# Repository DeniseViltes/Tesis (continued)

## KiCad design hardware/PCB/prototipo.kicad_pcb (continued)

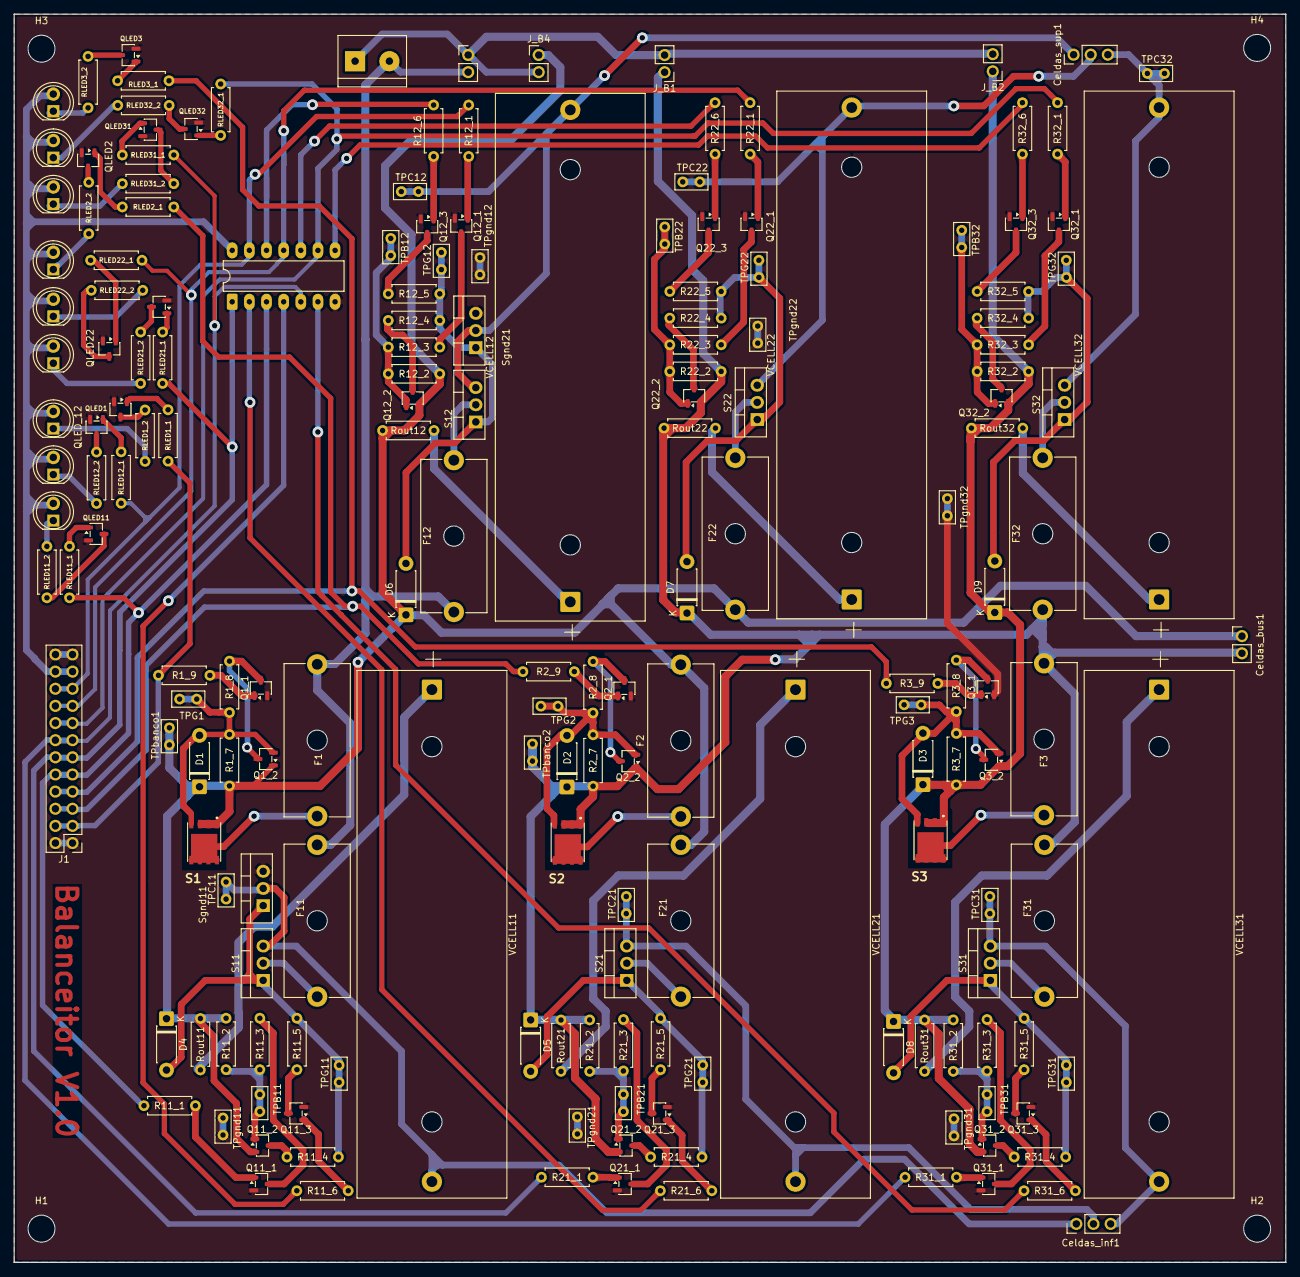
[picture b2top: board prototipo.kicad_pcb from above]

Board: 2 copper layers, 188.4 x 185.0 mm, 189 parts (0 on the bottom side), 121 nets.

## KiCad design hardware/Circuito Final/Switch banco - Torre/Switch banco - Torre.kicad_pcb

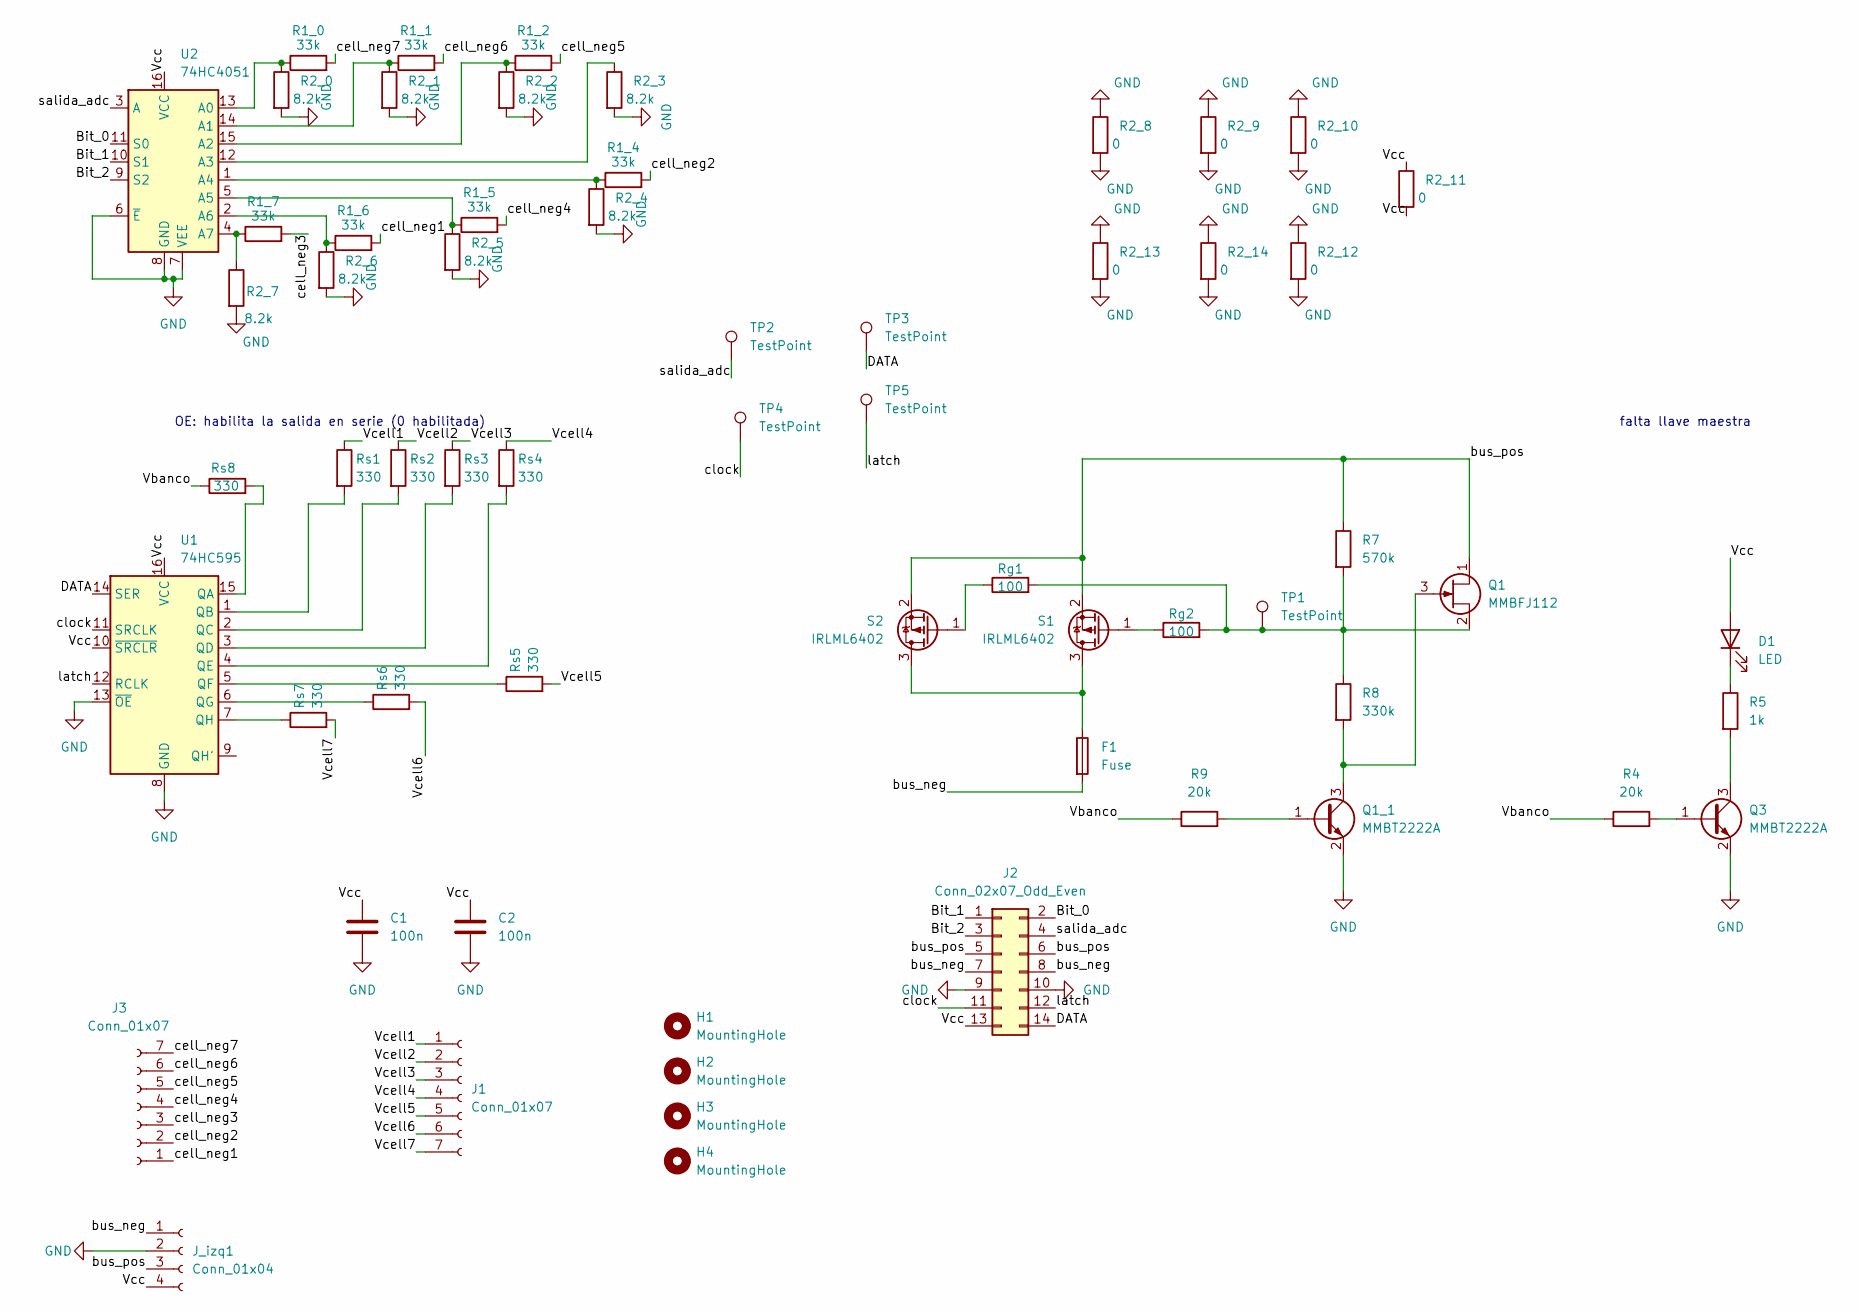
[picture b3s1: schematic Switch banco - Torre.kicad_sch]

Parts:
C1, C2: 100n; C_1206_3216Metric_Pad1.33x1.80mm_HandSolder
D1: LED; LED_D5.0mm
F1: Fuse; Fuse_1206_3216Metric_Pad1.42x1.75mm_HandSolder
H1, H2, H3, H4: MountingHole; MountingHole_3.5mm
J1, J3: Conn_01x07; PinSocket_1x07_P2.54mm_Vertical
J2: Conn_02x07_Odd_Even; IDC-Header_2x07_P2.54mm_Horizontal
J_izq1: Conn_01x04; PinSocket_1x04_P2.54mm_Vertical
Q1: MMBFJ112; SOT-23_Handsoldering
Q1_1, Q3: MMBT2222A; SOT-23_Handsoldering
R1_0, R1_1, R1_2, R1_4, R1_5, R1_6, R1_7: 33k; R_1206_3216Metric_Pad1.30x1.75mm_HandSolder
R2_0, R2_1, R2_2, R2_3, R2_4, R2_5, R2_6, R2_7: 8.2k; R_1206_3216Metric_Pad1.30x1.75mm_HandSolder
R2_8, R2_9, R2_10, R2_11, R2_12, R2_13, R2_14: 0; R_1206_3216Metric_Pad1.30x1.75mm_HandSolder
R4, R9: 20k; R_1206_3216Metric_Pad1.30x1.75mm_HandSolder
R5: 1k; R_1206_3216Metric_Pad1.30x1.75mm_HandSolder
R7: 570k; R_1206_3216Metric_Pad1.30x1.75mm_HandSolder
R8: 330k; R_1206_3216Metric_Pad1.30x1.75mm_HandSolder
Rg1, Rg2: 100; R_1206_3216Metric_Pad1.30x1.75mm_HandSolder
Rs1, Rs2, Rs3, Rs4, Rs5, Rs6, Rs7, Rs8: 330; R_1206_3216Metric_Pad1.30x1.75mm_HandSolder
S1, S2: IRLML6402; SOT-23_Handsoldering
TP1, TP2, TP3, TP4, TP5: TestPoint; TestPoint_Loop_D2.54mm_Drill1.5mm_Beaded
U1: 74HC595; SOIC-16_3.9x9.9mm_P1.27mm
U2: 74HC4051; SOIC-16_3.9x9.9mm_P1.27mm

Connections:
/Bit_0: J2.2, U2.11 (S0)
/Bit_1: J2.1, U2.10 (S1)
/Bit_2: J2.3, U2.9 (S2)
/DATA: J2.14, TP3.1 (1_1), U1.14 (SER)
/Vbanco: R4.1, R9.1, Rs8.1
/Vcc: C1.1, C2.1, D1.2 (A), J2.13, J_izq1.4, R2_11.1, R2_11.2, U1.10 (~SRCLR), U1.16 (VCC), U2.16 (VCC)
/Vcell1: J1.1, Rs1.1
/Vcell2: J1.2, Rs2.1
/Vcell3: J1.3, Rs3.1
/Vcell4: J1.4, Rs4.1
/Vcell5: J1.5, Rs5.2
/Vcell6: J1.6, Rs6.2
/Vcell7: J1.7, Rs7.2
/bus_neg: F1.2, J2.7, J2.8, J_izq1.1
/bus_pos: J2.5, J2.6, J_izq1.3, Q1.1 (D), R7.1, S1.2 (S), S2.2 (S)
/cell_neg1: J3.1, R1_6.2
/cell_neg2: J3.2, R1_4.2
/cell_neg3: J3.3, R1_7.2
/cell_neg4: J3.4, R1_5.2
/cell_neg5: J3.5, R1_2.2
/cell_neg6: J3.6, R1_1.2
/cell_neg7: J3.7, R1_0.2
/clock: J2.11, TP4.1 (1_1), U1.11 (SRCLK)
/latch: J2.12, TP5.1 (1_1), U1.12 (RCLK)
/salida_adc: J2.4, TP2.1 (1_1), U2.3 (A)
GND: C1.2, C2.2, J2.9, J2.10, J_izq1.2, Q1_1.2 (E), Q3.2 (E), R2_0.2, R2_1.2, R2_2.2, R2_3.2, R2_4.2, R2_5.2, R2_6.2, R2_7.2, R2_8.1, R2_8.2, R2_9.1, R2_9.2, R2_10.1, R2_10.2, R2_12.1, R2_12.2, R2_13.1, R2_13.2, R2_14.1, R2_14.2, U1.8 (GND), U1.13 (~OE), U2.6 (~E), U2.7 (VEE), U2.8 (GND)
unnamed: D1.1 (K), R5.1
unnamed: Q1.3 (G), Q1_1.3 (C), R8.2
unnamed: Q1.2 (S), R7.2, R8.1, Rg1.2, Rg2.2, TP1.1 (1_1)
unnamed: Q1_1.1 (B), R9.2
unnamed: Q3.1 (B), R4.2
unnamed: Q3.3 (C), R5.2
unnamed: F1.1, S1.3 (D), S2.3 (D)
unnamed: Rg2.1, S1.1 (G)
unnamed: Rg1.1, S2.1 (G)
unnamed: Rs8.2, U1.15 (QA)
unnamed: Rs1.2, U1.1 (QB)
unnamed: Rs2.2, U1.2 (QC)
unnamed: Rs3.2, U1.3 (QD)
unnamed: Rs4.2, U1.4 (QE)
unnamed: Rs5.1, U1.5 (QF)
unnamed: Rs6.1, U1.6 (QG)
unnamed: Rs7.1, U1.7 (QH)
unnamed: R1_0.1, R2_0.1, U2.13 (A0)
unnamed: R1_1.1, R2_1.1, U2.14 (A1)
unnamed: R1_2.1, R2_2.1, U2.15 (A2)
unnamed: R2_3.1, U2.12 (A3)
unnamed: R1_4.1, R2_4.1, U2.1 (A4)
unnamed: R1_5.1, R2_5.1, U2.5 (A5)
unnamed: R1_6.1, R2_6.1, U2.2 (A6)
unnamed: R1_7.1, R2_7.1, U2.4 (A7)

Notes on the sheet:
falta llave maestra
OE: habilita la salida en serie (0 habilitada)

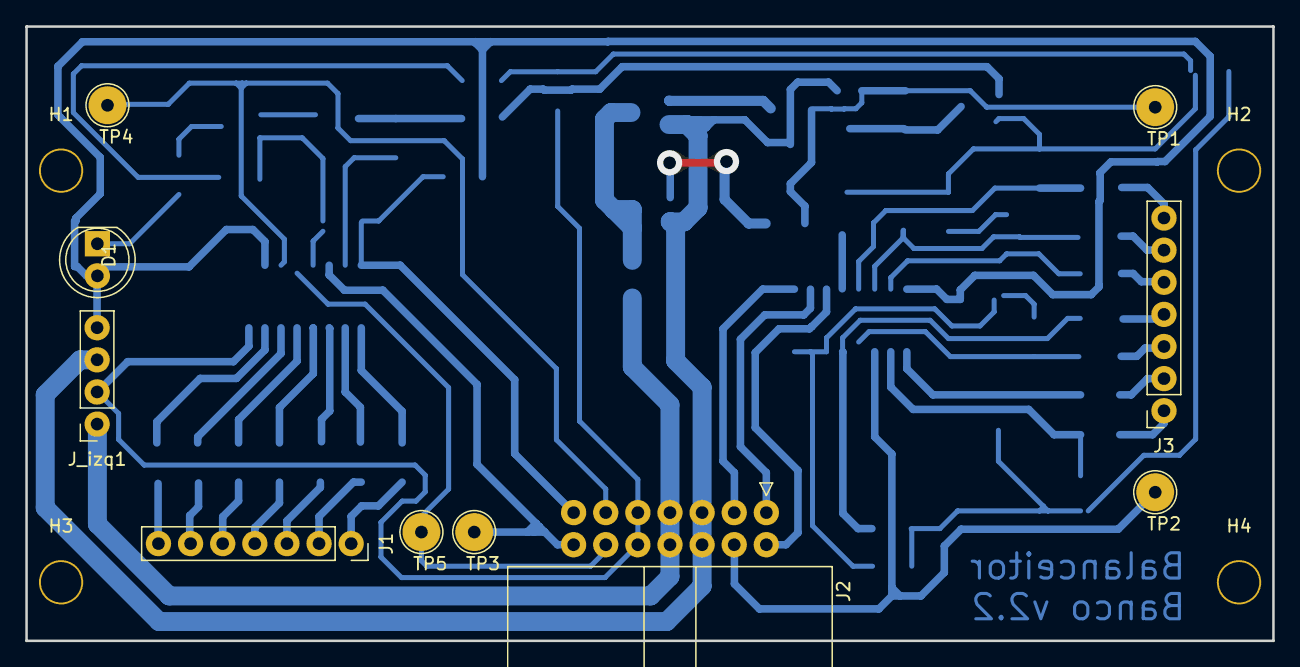
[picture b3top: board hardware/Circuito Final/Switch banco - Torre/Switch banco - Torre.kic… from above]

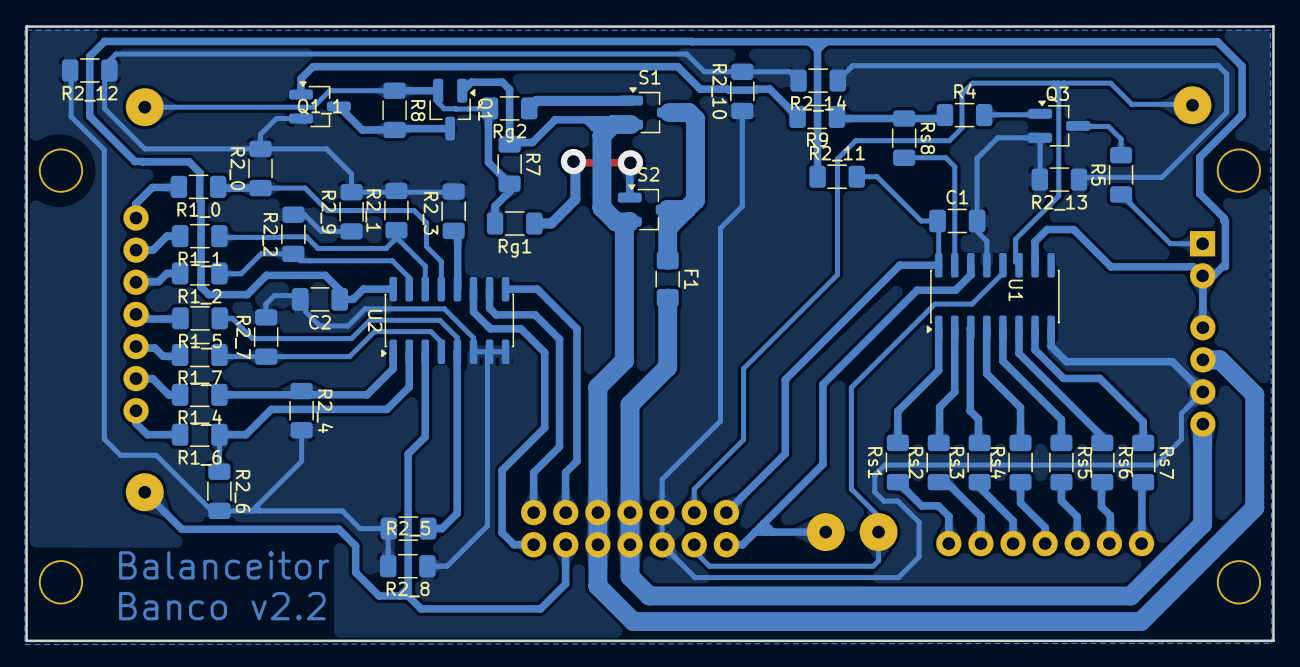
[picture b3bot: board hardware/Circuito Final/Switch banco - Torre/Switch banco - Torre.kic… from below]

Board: 2 copper layers, 98.6 x 48.6 mm, 61 parts (47 on the bottom side), 51 nets.

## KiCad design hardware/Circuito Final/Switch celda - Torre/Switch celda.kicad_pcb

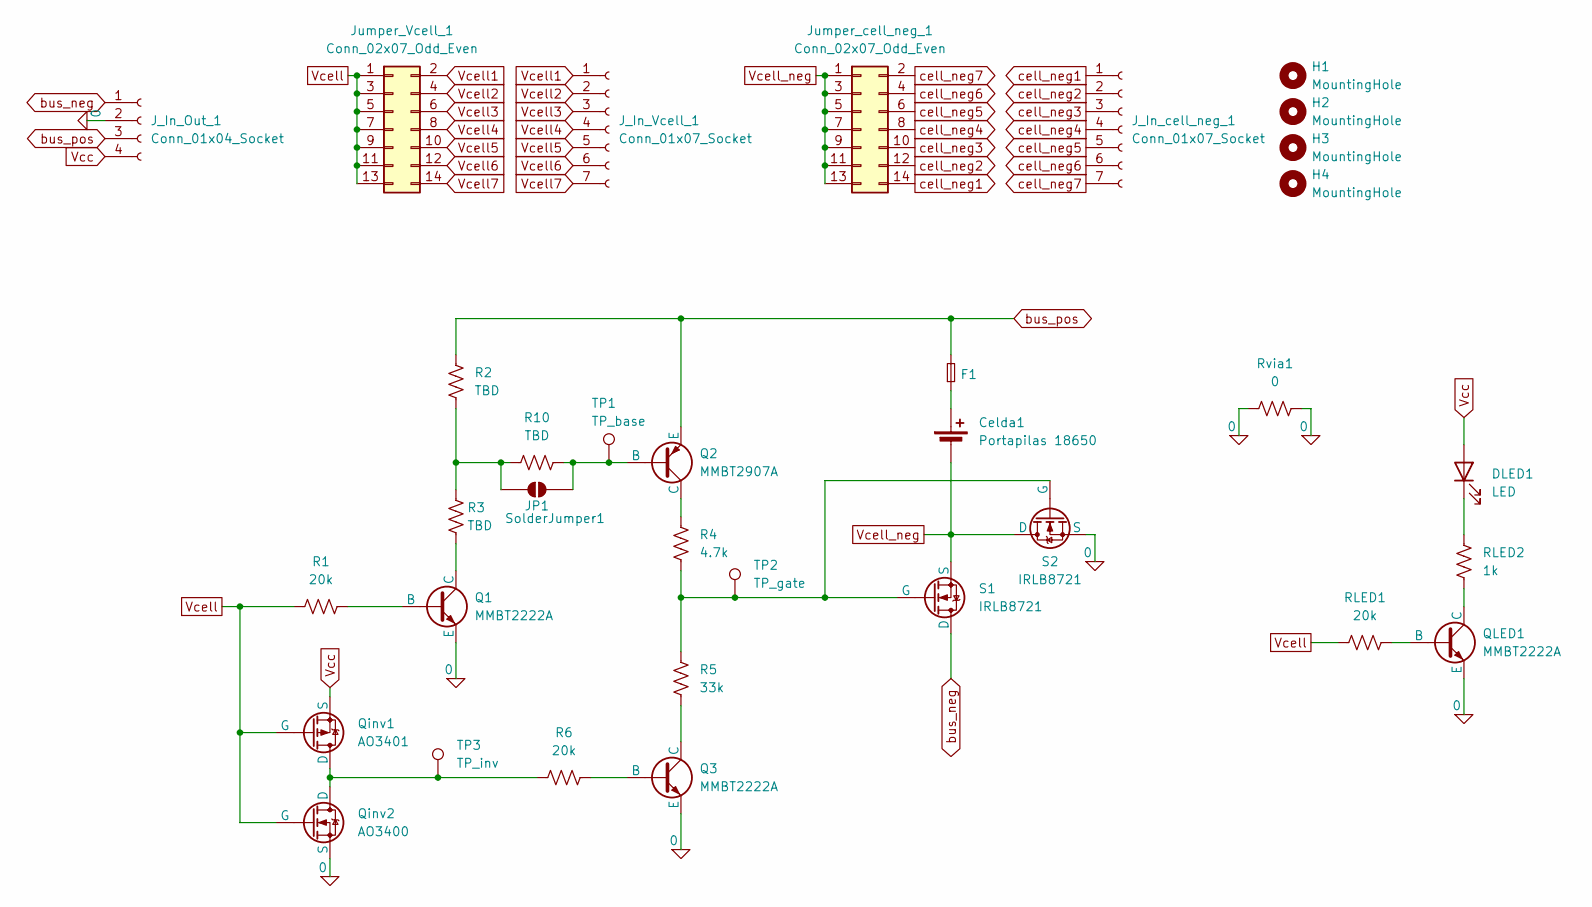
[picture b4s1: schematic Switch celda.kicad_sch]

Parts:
Celda1: Portapilas 18650; BatteryHolder_MPD_BK-18650-PC2
DLED1: LED; LED_D5.0mm
F1: Fuse_1206_3216Metric_Pad1.42x1.75mm_HandSolder
H1, H2, H3, H4: MountingHole; MountingHole_3.5mm
JP1: SolderJumper1; SolderJumper-2_P1.3mm_Open_TrianglePad1.0x1.5mm
J_In_Out_1: Conn_01x04_Socket; PinSocket_1x04_P2.54mm_Vertical
J_In_Vcell_1: Conn_01x07_Socket; PinSocket_1x07_P2.54mm_Vertical
J_In_cell_neg_1: Conn_01x07_Socket; PinSocket_1x07_P2.54mm_Vertical
Jumper_Vcell_1: Conn_02x07_Odd_Even; PinHeader_2x07_P2.54mm_Vertical
Jumper_cell_neg_1: Conn_02x07_Odd_Even; PinHeader_2x07_P2.54mm_Vertical
Q1, Q3: MMBT2222A; SOT-23_Handsoldering
Q2: MMBT2907A; SOT-23_Handsoldering
QLED1: MMBT2222A; SOT-23_Handsoldering
Qinv1: AO3401; SOT-23_Handsoldering
Qinv2: AO3400; SOT-23_Handsoldering
R1, R6: 20k; R_1206_3216Metric_Pad1.30x1.75mm_HandSolder
R2, R3, R10: TBD; R_1206_3216Metric_Pad1.30x1.75mm_HandSolder
R4: 4.7k; R_1206_3216Metric_Pad1.30x1.75mm_HandSolder
R5: 33k; R_1206_3216Metric_Pad1.30x1.75mm_HandSolder
RLED1: 20k; R_1206_3216Metric_Pad1.30x1.75mm_HandSolder
RLED2: 1k; R_1206_3216Metric_Pad1.30x1.75mm_HandSolder
Rvia1: 0; R_1206_3216Metric_Pad1.30x1.75mm_HandSolder
S1, S2: IRLB8721; TO-220-3_Vertical
TP1: TP_base; TestPoint_Loop_D2.54mm_Drill1.5mm_Beaded
TP2: TP_gate; TestPoint_Loop_D2.54mm_Drill1.5mm_Beaded
TP3: TP_inv; TestPoint_Loop_D2.54mm_Drill1.5mm_Beaded

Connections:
0: J_In_Out_1.2, Q1.3 (E), Q3.3 (E), QLED1.3 (E), Qinv2.3 (S), Rvia1.1, Rvia1.2, S2.3 (S)
unnamed: Celda1.1 (+), F1.1
unnamed: DLED1.1 (K), RLED2.2
unnamed: JP1.1 (A), R2.1, R3.2, R10.1
unnamed: JP1.2 (B), Q2.2 (B), R10.2, TP1.1 (1_1)
unnamed: Q1.2 (B), R1.2
unnamed: Q1.1 (C), R3.1
unnamed: Q2.1 (C), R4.2
unnamed: Q3.2 (B), R6.2
unnamed: Q3.1 (C), R5.1
unnamed: QLED1.2 (B), RLED1.2
unnamed: QLED1.1 (C), RLED2.1
unnamed: Qinv1.1 (D), Qinv2.1 (D), R6.1, TP3.1 (1_1)
unnamed: R4.1, R5.2, S1.2 (G), S2.2 (G), TP2.1 (1_1)
Vcc: DLED1.2 (A), J_In_Out_1.4, Qinv1.3 (S)
Vcell: Jumper_Vcell_1.1, Jumper_Vcell_1.3, Jumper_Vcell_1.5, Jumper_Vcell_1.7, Jumper_Vcell_1.9, Jumper_Vcell_1.11, Jumper_Vcell_1.13, Qinv1.2 (G), Qinv2.2 (G), R1.1, RLED1.1
Vcell1: J_In_Vcell_1.1, Jumper_Vcell_1.2
Vcell2: J_In_Vcell_1.2, Jumper_Vcell_1.4
Vcell3: J_In_Vcell_1.3, Jumper_Vcell_1.6
Vcell4: J_In_Vcell_1.4, Jumper_Vcell_1.8
Vcell5: J_In_Vcell_1.5, Jumper_Vcell_1.10
Vcell6: J_In_Vcell_1.6, Jumper_Vcell_1.12
Vcell7: J_In_Vcell_1.7, Jumper_Vcell_1.14
Vcell_neg: Celda1.2 (-), Jumper_cell_neg_1.1, Jumper_cell_neg_1.3, Jumper_cell_neg_1.5, Jumper_cell_neg_1.7, Jumper_cell_neg_1.9, Jumper_cell_neg_1.11, Jumper_cell_neg_1.13, S1.3 (S), S2.1 (D)
bus_neg: J_In_Out_1.1, S1.1 (D)
bus_pos: F1.2, J_In_Out_1.3, Q2.3 (E), R2.2
cell_neg1: J_In_cell_neg_1.1, Jumper_cell_neg_1.14
cell_neg2: J_In_cell_neg_1.2, Jumper_cell_neg_1.12
cell_neg3: J_In_cell_neg_1.3, Jumper_cell_neg_1.10
cell_neg4: J_In_cell_neg_1.4, Jumper_cell_neg_1.8
cell_neg5: J_In_cell_neg_1.5, Jumper_cell_neg_1.6
cell_neg6: J_In_cell_neg_1.6, Jumper_cell_neg_1.4
cell_neg7: J_In_cell_neg_1.7, Jumper_cell_neg_1.2

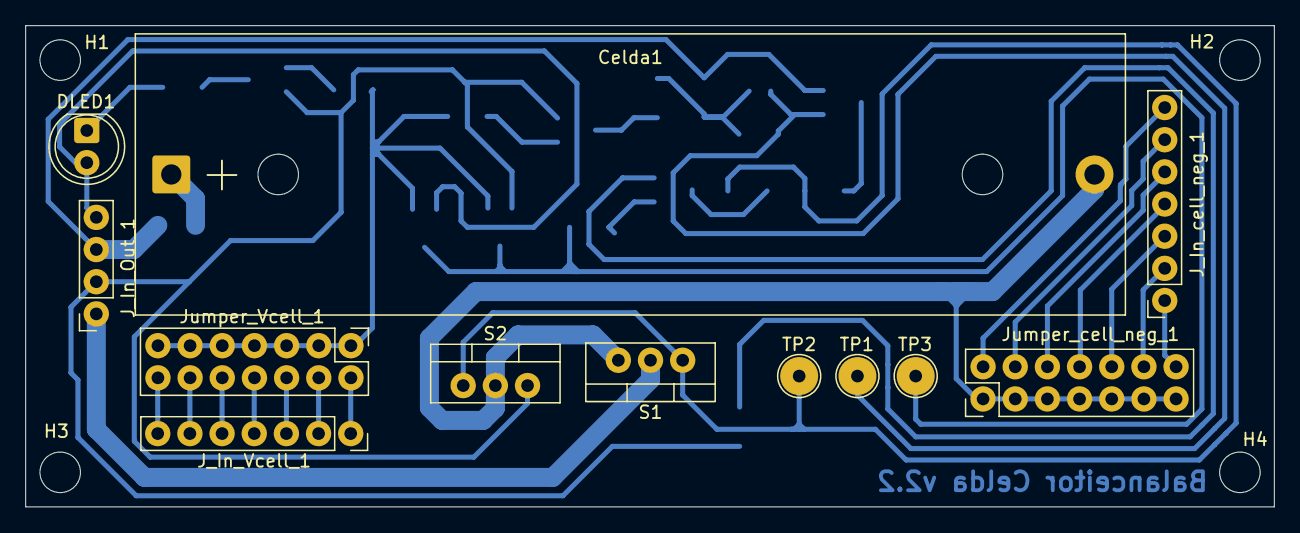
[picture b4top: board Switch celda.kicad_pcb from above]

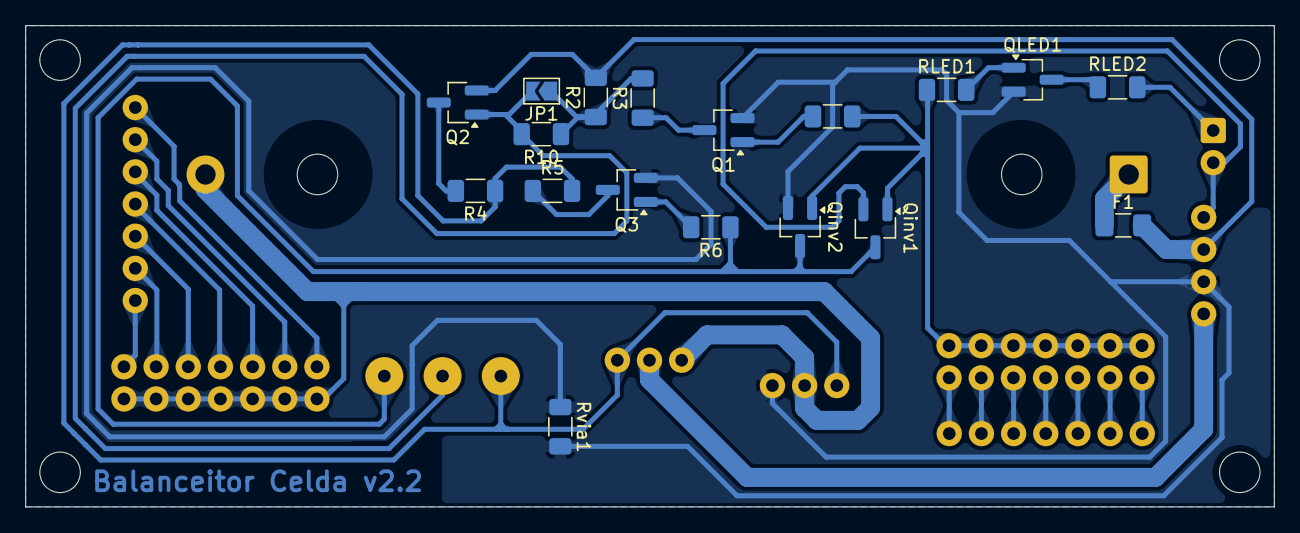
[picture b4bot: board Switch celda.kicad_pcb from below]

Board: 2 copper layers, 98.6 x 38.0 mm, 34 parts (18 on the bottom side), 33 nets.

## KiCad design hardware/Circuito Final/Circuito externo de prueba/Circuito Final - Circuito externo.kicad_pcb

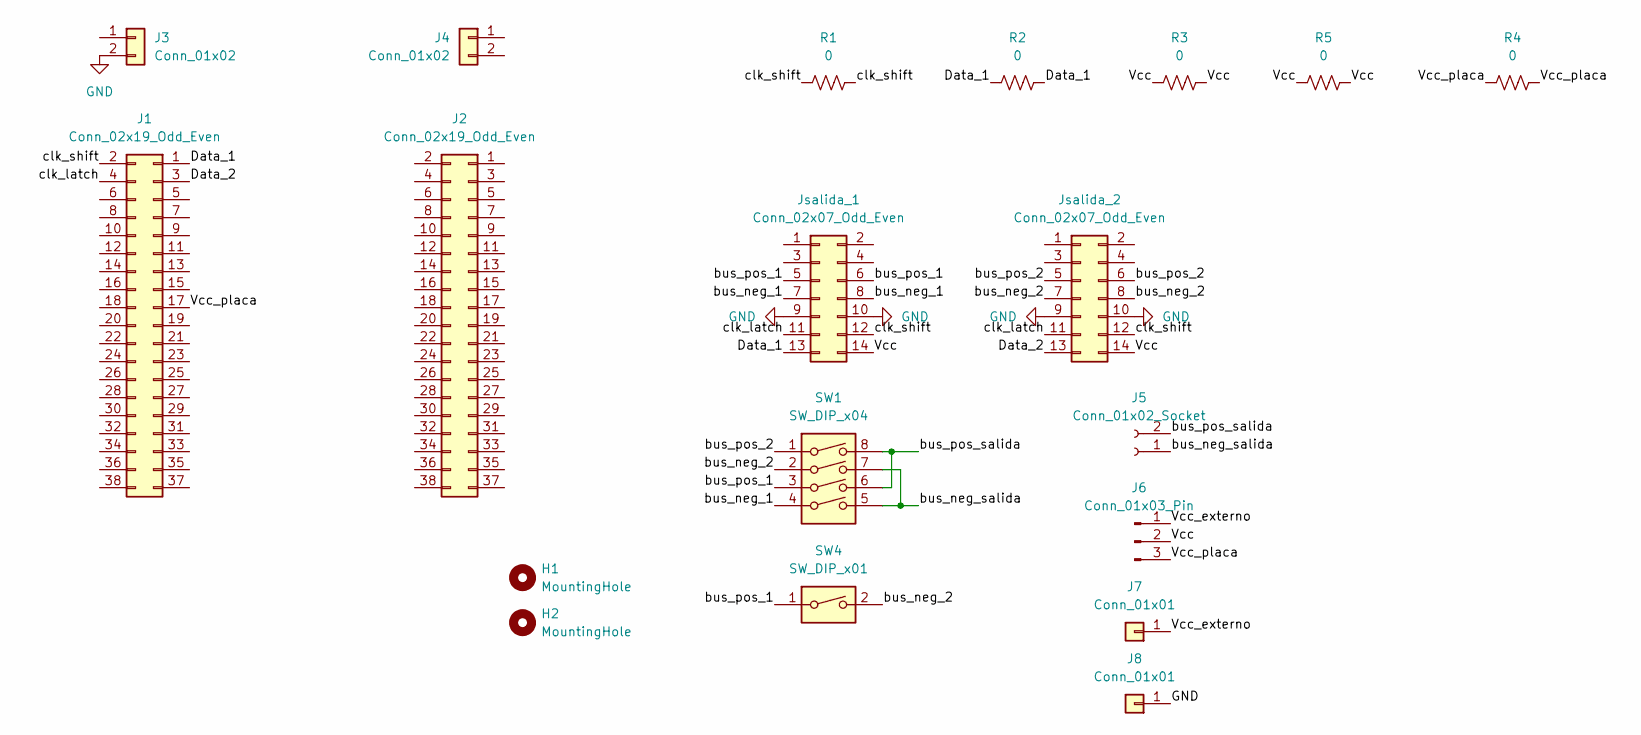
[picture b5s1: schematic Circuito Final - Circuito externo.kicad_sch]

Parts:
H1, H2: MountingHole; MountingHole_3mm
J1, J2: Conn_02x19_Odd_Even; PinSocket_2x19_P2.54mm_Vertical
J3, J4: Conn_01x02; PinSocket_1x02_P2.54mm_Vertical
J5: Conn_01x02_Socket; TerminalBlock_MaiXu_MX126-5.0-02P_1x02_P5.00mm
J6: Conn_01x03_Pin; PinHeader_1x03_P2.54mm_Vertical
J7, J8: Conn_01x01; PinHeader_1x01_P2.54mm_Vertical
Jsalida_1, Jsalida_2: Conn_02x07_Odd_Even; PinHeader_2x07_P2.54mm_Vertical
R1, R2, R3, R4, R5: 0; R_1206_3216Metric_Pad1.30x1.75mm_HandSolder
SW1: SW_DIP_x04; SW_DIP_SPSTx04_Slide_9.78x12.34mm_W7.62mm_P2.54mm
SW4: SW_DIP_x01; SW_DIP_SPSTx01_Slide_9.78x4.72mm_W7.62mm_P2.54mm

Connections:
/Data_1: J1.1, Jsalida_1.13, R2.1, R2.2
/Data_2: J1.3, Jsalida_2.13
/Vcc: J6.2, Jsalida_1.14, Jsalida_2.14, R3.1, R3.2, R5.1, R5.2
/Vcc_externo: J6.1, J7.1 (Pin_1_1)
/Vcc_placa: J1.17, J6.3, R4.1, R4.2
/bus_neg_1: Jsalida_1.7, Jsalida_1.8, SW1.4
/bus_neg_2: Jsalida_2.7, Jsalida_2.8, SW1.2, SW4.2
/bus_neg_salida: J5.1, SW1.5, SW1.7
/bus_pos_1: Jsalida_1.5, Jsalida_1.6, SW1.3, SW4.1
/bus_pos_2: Jsalida_2.5, Jsalida_2.6, SW1.1
/bus_pos_salida: J5.2, SW1.6, SW1.8
/clk_latch: J1.4, Jsalida_1.11, Jsalida_2.11
/clk_shift: J1.2, Jsalida_1.12, Jsalida_2.12, R1.1, R1.2
GND: J3.2 (Pin_2_2), J8.1 (Pin_1_1), Jsalida_1.9, Jsalida_1.10, Jsalida_2.9, Jsalida_2.10

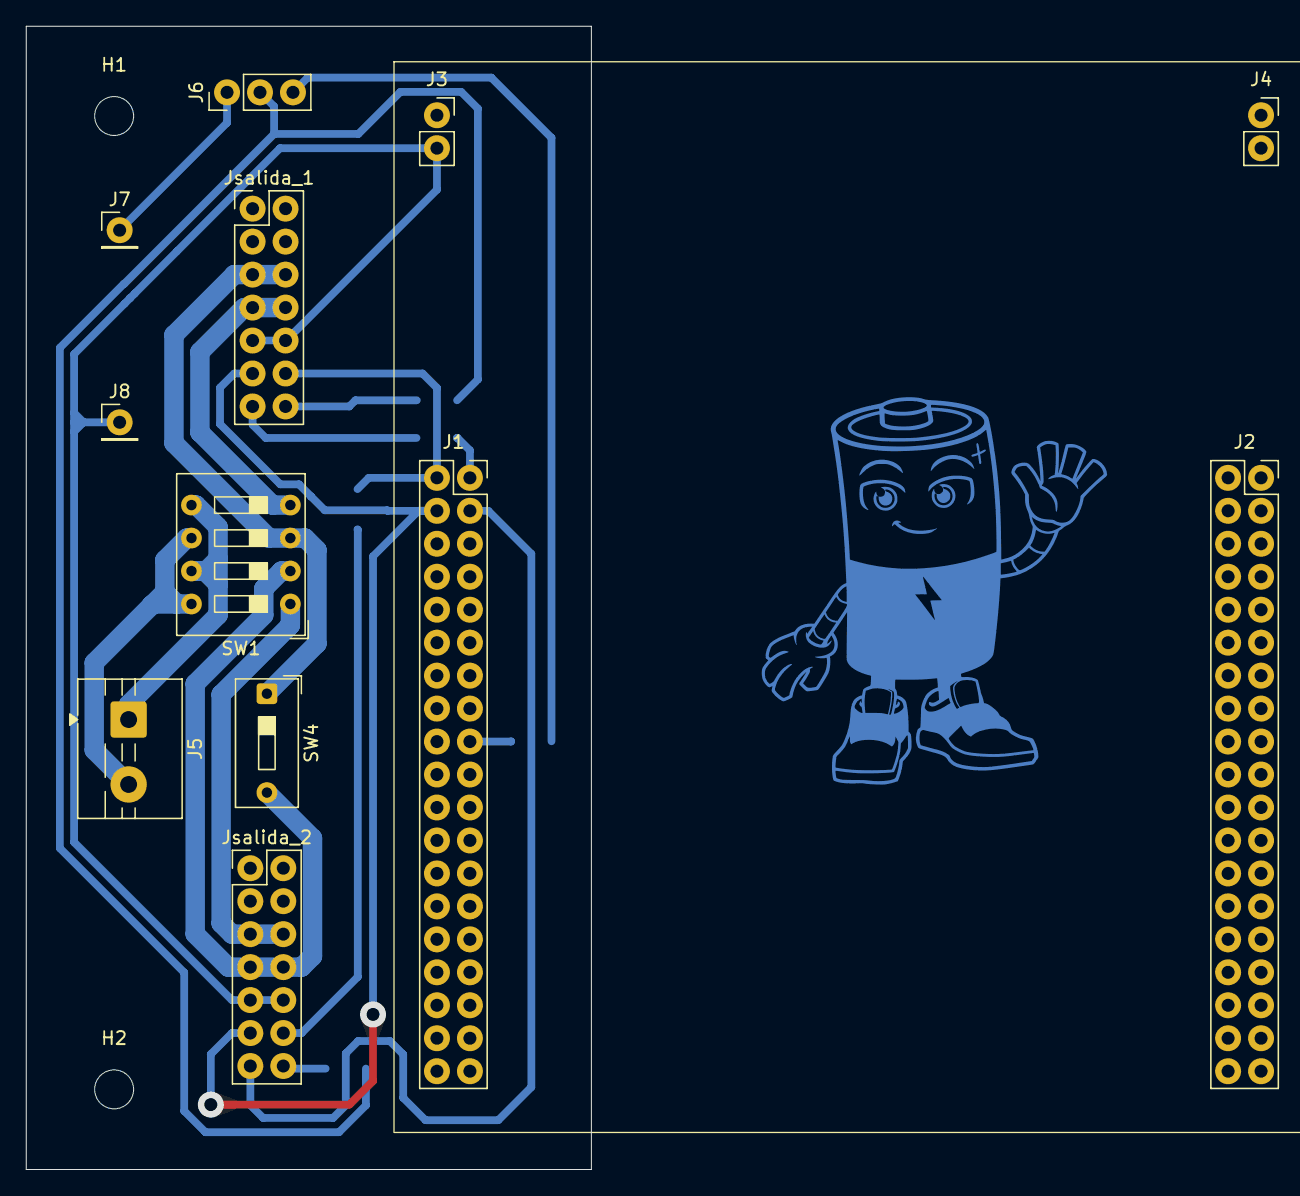
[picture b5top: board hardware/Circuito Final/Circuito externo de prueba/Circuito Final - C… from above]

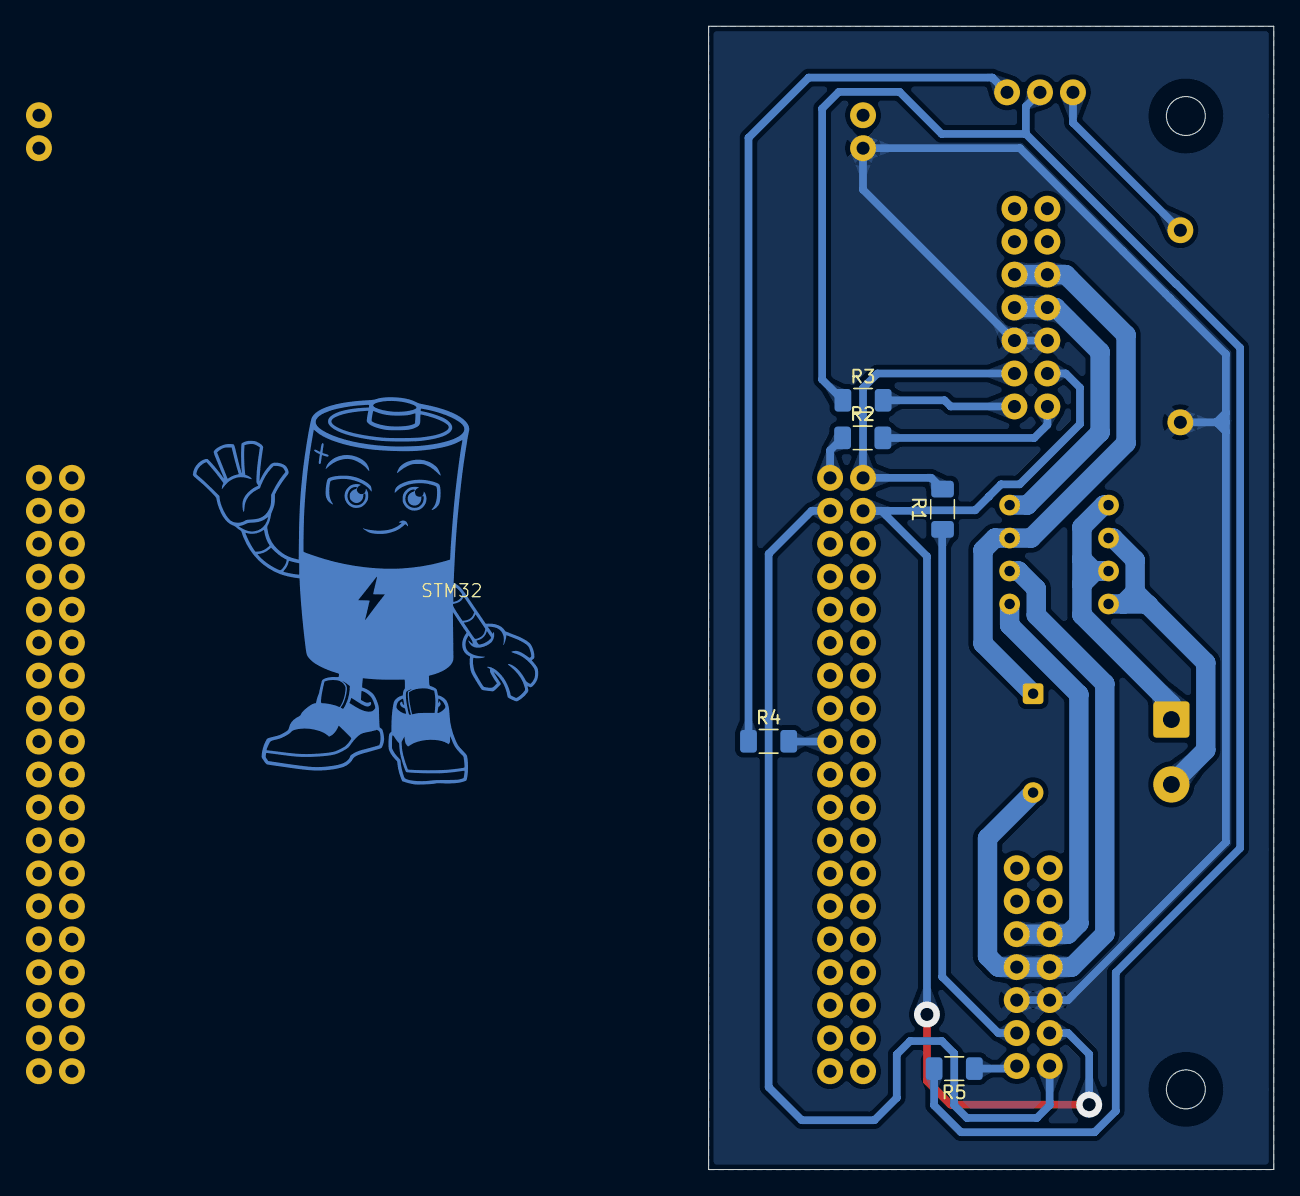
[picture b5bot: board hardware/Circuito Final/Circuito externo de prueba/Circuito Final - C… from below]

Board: 2 copper layers, 43.5 x 88.1 mm, 20 parts (5 on the bottom side), 14 nets.

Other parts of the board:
STM32: STM32

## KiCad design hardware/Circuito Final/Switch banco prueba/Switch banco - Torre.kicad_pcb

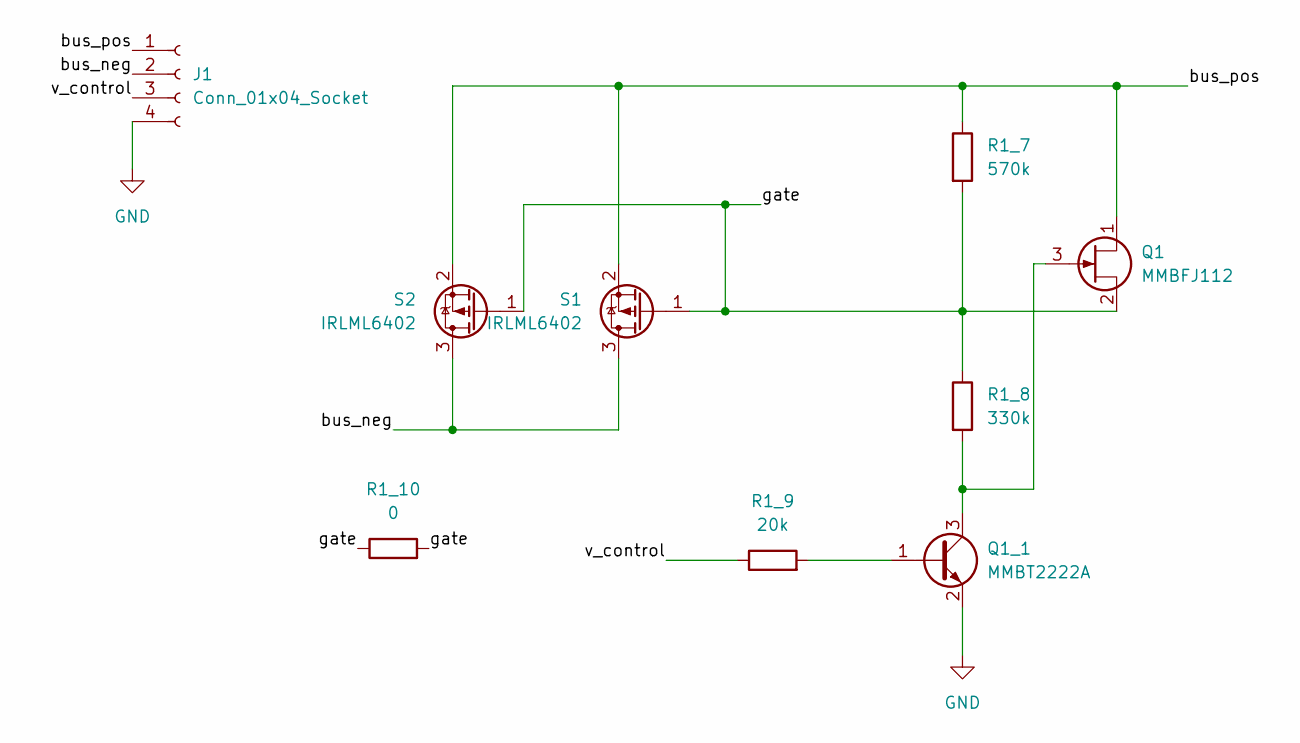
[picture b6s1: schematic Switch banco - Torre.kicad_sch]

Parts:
J1: Conn_01x04_Socket; PinSocket_1x04_P2.54mm_Vertical
Q1: MMBFJ112; SOT-23
Q1_1: MMBT2222A; SOT-23
R1_7: 570k; R_1206_3216Metric_Pad1.30x1.75mm_HandSolder
R1_8: 330k; R_1206_3216Metric_Pad1.30x1.75mm_HandSolder
R1_9: 20k; R_1206_3216Metric_Pad1.30x1.75mm_HandSolder
R1_10: 0; R_1206_3216Metric_Pad1.30x1.75mm_HandSolder
S1, S2: IRLML6402; SOT-23

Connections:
/bus_neg: J1.2, S1.3 (D), S2.3 (D)
/bus_pos: J1.1, Q1.1 (D), R1_7.1, S1.2 (S), S2.2 (S)
/gate: Q1.2 (S), R1_7.2, R1_8.1, R1_10.1, R1_10.2, S1.1 (G), S2.1 (G)
/v_control: J1.3, R1_9.1
GND: J1.4, Q1_1.2 (E)
unnamed: Q1.3 (G), Q1_1.3 (C), R1_8.2
unnamed: Q1_1.1 (B), R1_9.2

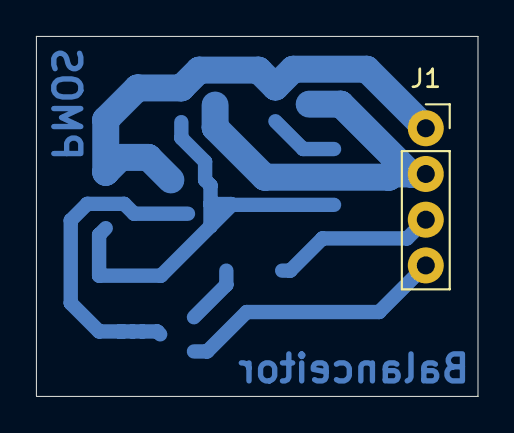
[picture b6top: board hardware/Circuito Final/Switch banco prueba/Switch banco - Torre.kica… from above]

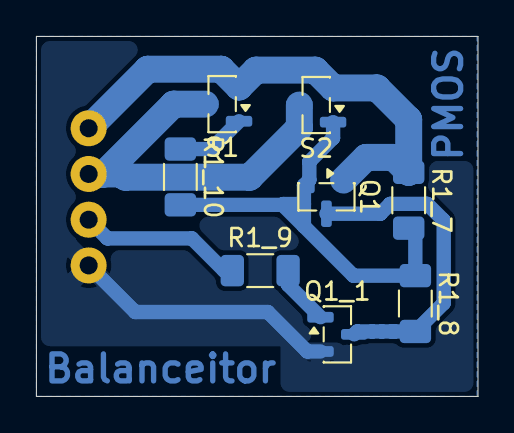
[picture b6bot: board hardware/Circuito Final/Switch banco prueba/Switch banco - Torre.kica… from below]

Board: 2 copper layers, 24.5 x 20.0 mm, 9 parts (8 on the bottom side), 7 nets.

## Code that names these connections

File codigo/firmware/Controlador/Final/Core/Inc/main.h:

/* USER CODE BEGIN Header */
/**
  ******************************************************************************
  * @file           : main.h
  * @brief          : Header for main.c file.
  *                   This file contains the common defines of the application.
  ******************************************************************************
  * @attention
  *
  * Copyright (c) 2026 STMicroelectronics.
  * All rights reserved.
  *
  * This software is licensed under terms that can be found in the LICENSE file
  * in the root directory of this software component.
  * If no LICENSE file comes with this software, it is provided AS-IS.
  *
  ******************************************************************************
  */
/* USER CODE END Header */

/* Define to prevent recursive inclusion -------------------------------------*/
#ifndef __MAIN_H
#define __MAIN_H

#ifdef __cplusplus
extern "C" {
#endif

/* Includes ------------------------------------------------------------------*/
#include "stm32f1xx_hal.h"

/* Private includes ----------------------------------------------------------*/
/* USER CODE BEGIN Includes */

/* USER CODE END Includes */

/* Exported types ------------------------------------------------------------*/
/* USER CODE BEGIN ET */

/* USER CODE END ET */

/* Exported constants --------------------------------------------------------*/
/* USER CODE BEGIN EC */

/* USER CODE END EC */

/* Exported macro ------------------------------------------------------------*/
/* USER CODE BEGIN EM */

/* USER CODE END EM */

/* Exported functions prototypes ---------------------------------------------*/
void Error_Handler(void);

/* USER CODE BEGIN EFP */

/* USER CODE END EFP */

/* Private defines -----------------------------------------------------------*/
#define DATA2_Pin GPIO_PIN_13
#define DATA2_GPIO_Port GPIOC
#define medicion_corriente_de_carga_Pin GPIO_PIN_0
#define medicion_corriente_de_carga_GPIO_Port GPIOC
#define salida_adc_2_Pin GPIO_PIN_2
#define salida_adc_2_GPIO_Port GPIOC
#define banco2_med_Pin GPIO_PIN_3
#define banco2_med_GPIO_Port GPIOC
#define Salida_adc_1_Pin GPIO_PIN_0
#define Salida_adc_1_GPIO_Port GPIOA
#define banco1_med_Pin GPIO_PIN_1
#define banco1_med_GPIO_Port GPIOA
#define USART_TX_Pin GPIO_PIN_2
#define USART_TX_GPIO_Port GPIOA
#define USART_RX_Pin GPIO_PIN_3
#define USART_RX_GPIO_Port GPIOA
#define banco4_med_Pin GPIO_PIN_5
#define banco4_med_GPIO_Port GPIOA
#define medicion_corriente_descarga_Pin GPIO_PIN_6
#define medicion_corriente_descarga_GPIO_Port GPIOA
#define banco3_med_Pin GPIO_PIN_7
#define banco3_med_GPIO_Port GPIOA
#define salida_adc_3_Pin GPIO_PIN_4
#define salida_adc_3_GPIO_Port GPIOC
#define Salida_adc_4_Pin GPIO_PIN_5
#define Salida_adc_4_GPIO_Port GPIOC
#define S2_Pin GPIO_PIN_6
#define S2_GPIO_Port GPIOC
#define S1_Pin GPIO_PIN_8
#define S1_GPIO_Port GPIOC
#define S0_Pin GPIO_PIN_9
#define S0_GPIO_Port GPIOC
#define llave_de_emergencia_Pin GPIO_PIN_10
#define llave_de_emergencia_GPIO_Port GPIOA
#define DATA3_Pin GPIO_PIN_11
#define DATA3_GPIO_Port GPIOA
#define DATA4_Pin GPIO_PIN_12
#define DATA4_GPIO_Port GPIOA
#define TMS_Pin GPIO_PIN_13
#define TMS_GPIO_Port GPIOA
#define TCK_Pin GPIO_PIN_14
#define TCK_GPIO_Port GPIOA
#define BUZZER_Pin GPIO_PIN_15
#define BUZZER_GPIO_Port GPIOA
#define CLK_Pin GPIO_PIN_10
#define CLK_GPIO_Port GPIOC
#define LATCH_Pin GPIO_PIN_11
#define LATCH_GPIO_Port GPIOC
#define DATA1_Pin GPIO_PIN_12
#define DATA1_GPIO_Port GPIOC

/* USER CODE BEGIN Private defines */
#define BUZZER_Pin GPIO_PIN_15
#define BUZZER_GPIO_Port GPIOA

/* USER CODE END Private defines */

#ifdef __cplusplus
}
#endif

#endif /* __MAIN_H */

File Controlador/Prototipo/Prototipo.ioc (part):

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Mcu.Name=STM32F103R(8-B)Tx
Mcu.Package=LQFP64
Mcu.UserName=STM32F103RBTx
PA0-WKUP.GPIOParameters=GPIO_Label
PA0-WKUP.GPIO_Label=cell_11
PA0-WKUP.Signal=ADCx_IN0
PA1.GPIOParameters=GPIO_Label
PA1.GPIO_Label=cell_12
PA1.Signal=ADCx_IN1
PA13.GPIOParameters=GPIO_Label
PA13.GPIO_Label=TMS
PA13.Mode=Serial_Wire
PA13.Signal=SYS_JTMS-SWDIO
PA14.GPIOParameters=GPIO_Label
PA14.GPIO_Label=TCK
PA14.Mode=Serial_Wire
PA14.Signal=SYS_JTCK-SWCLK
PA2.GPIOParameters=GPIO_Speed,GPIO_PuPd,GPIO_Label,GPIO_Mode
PA2.GPIO_Label=USART_TX
PA2.GPIO_Mode=GPIO_MODE_AF_PP
PA2.GPIO_PuPd=GPIO_NOPULL
PA2.GPIO_Speed=GPIO_SPEED_FREQ_LOW
PA2.Mode=Asynchronous
PA2.Signal=USART2_TX
PA3.GPIOParameters=GPIO_Speed,GPIO_PuPd,GPIO_Label,GPIO_Mode
PA3.GPIO_Label=USART_RX
PA3.GPIO_Mode=GPIO_MODE_INPUT
PA3.GPIO_PuPd=GPIO_NOPULL
PA3.GPIO_Speed=GPIO_SPEED_FREQ_LOW
PA3.Mode=Asynchronous
PA3.Signal=USART2_RX
PA4.GPIOParameters=GPIO_Label
PA4.GPIO_Label=cell_21
PA4.Signal=ADCx_IN4
PA5.GPIOParameters=GPIO_Label
PA5.GPIO_Label=bus_1
PA5.Signal=ADCx_IN5
PA6.GPIOParameters=GPIO_Label
PA6.GPIO_Label=out_neg
PA6.Signal=ADCx_IN6
PA7.GPIOParameters=GPIO_Label
PA7.GPIO_Label=out_pos
PA7.Signal=ADCx_IN7
PB0.GPIOParameters=GPIO_Label
PB0.GPIO_Label=cell_22
PB0.Signal=ADCx_IN8
PB10.GPIOParameters=PinState,GPIO_PuPd,GPIO_Label
PB10.GPIO_Label=Vc_31
PB10.GPIO_PuPd=GPIO_PULLDOWN
PB10.PinState=GPIO_PIN_RESET
PB10.Signal=GPIO_Output
PB11.GPIOParameters=PinState,GPIO_PuPd,GPIO_Label
PB11.GPIO_Label=Vc_32
PB11.GPIO_PuPd=GPIO_PULLDOWN
PB11.PinState=GPIO_PIN_RESET
PB11.Signal=GPIO_Output
PB12.GPIOParameters=PinState,GPIO_PuPd,GPIO_Label
PB12.GPIO_Label=Vc_12
PB12.GPIO_PuPd=GPIO_PULLDOWN
PB12.PinState=GPIO_PIN_RESET
PB12.Signal=GPIO_Output
PB3.GPIOParameters=PinState,GPIO_PuPd,GPIO_Label,GPIO_ModeDefaultOutputPP
PB3.GPIO_Label=Vc_1
PB3.GPIO_ModeDefaultOutputPP=GPIO_MODE_OUTPUT_PP
PB3.GPIO_PuPd=GPIO_PULLDOWN
PB3.PinState=GPIO_PIN_RESET
PB3.Signal=GPIO_Output
PB4.GPIOParameters=PinState,GPIO_PuPd,GPIO_Label,GPIO_ModeDefaultOutputPP
PB4.GPIO_Label=Vc_2
PB4.GPIO_ModeDefaultOutputPP=GPIO_MODE_OUTPUT_PP
PB4.GPIO_PuPd=GPIO_PULLDOWN
PB4.PinState=GPIO_PIN_RESET
PB4.Signal=GPIO_Output
PB5.GPIOParameters=PinState,GPIO_PuPd,GPIO_Label,GPIO_ModeDefaultOutputPP
PB5.GPIO_Label=Vc_3
PB5.GPIO_ModeDefaultOutputPP=GPIO_MODE_OUTPUT_PP
PB5.GPIO_PuPd=GPIO_PULLDOWN
PB5.PinState=GPIO_PIN_RESET
PB5.Signal=GPIO_Output
PB6.GPIOParameters=PinState,GPIO_PuPd,GPIO_Label
PB6.GPIO_Label=Vc_11
PB6.GPIO_PuPd=GPIO_PULLDOWN
PB6.PinState=GPIO_PIN_RESET
PB6.Signal=GPIO_Output
PB8.GPIOParameters=PinState,GPIO_PuPd,GPIO_Label
PB8.GPIO_Label=Vc_21
PB8.GPIO_PuPd=GPIO_PULLDOWN
PB8.PinState=GPIO_PIN_RESET
PB8.Signal=GPIO_Output
PB9.GPIOParameters=PinState,GPIO_PuPd,GPIO_Label
PB9.GPIO_Label=Vc_22
PB9.GPIO_PuPd=GPIO_PULLDOWN
PB9.PinState=GPIO_PIN_RESET
PB9.Signal=GPIO_Output
PC0.GPIOParameters=GPIO_Label
PC0.GPIO_Label=cell_31
PC0.Signal=ADCx_IN10
PC1.GPIOParameters=GPIO_Label
PC1.GPIO_Label=cell_32
PC1.Signal=ADCx_IN11
PC13-TAMPER-RTC.GPIOParameters=GPIO_PuPd,GPIO_Label
PC13-TAMPER-RTC.GPIO_Label=B1 [Blue PushButton]
PC13-TAMPER-RTC.GPIO_PuPd=GPIO_NOPULL
PC13-TAMPER-RTC.Signal=GPXTI13
PC14-OSC32_IN.Mode=LSE-External-Oscillator
PC14-OSC32_IN.Signal=RCC_OSC32_IN
PC15-OSC32_OUT.Mode=LSE-External-Oscillator
PC15-OSC32_OUT.Signal=RCC_OSC32_OUT
PC4.GPIOParameters=GPIO_Label
PC4.GPIO_Label=bus_2
PC4.Signal=ADCx_IN14
PD0-OSC_IN.Mode=HSE-External-Clock-Source
PD0-OSC_IN.Signal=RCC_OSC_IN
PD1-OSC_OUT.Mode=HSE-External-Clock-Source
PD1-OSC_OUT.Signal=RCC_OSC_OUT
RCC.SYSCLKFreq_VALUE=8000000
RCC.SYSCLKSource=RCC_SYSCLKSOURCE_PLLCLK
board=NUCLEO-F103RB
boardIOC=true
